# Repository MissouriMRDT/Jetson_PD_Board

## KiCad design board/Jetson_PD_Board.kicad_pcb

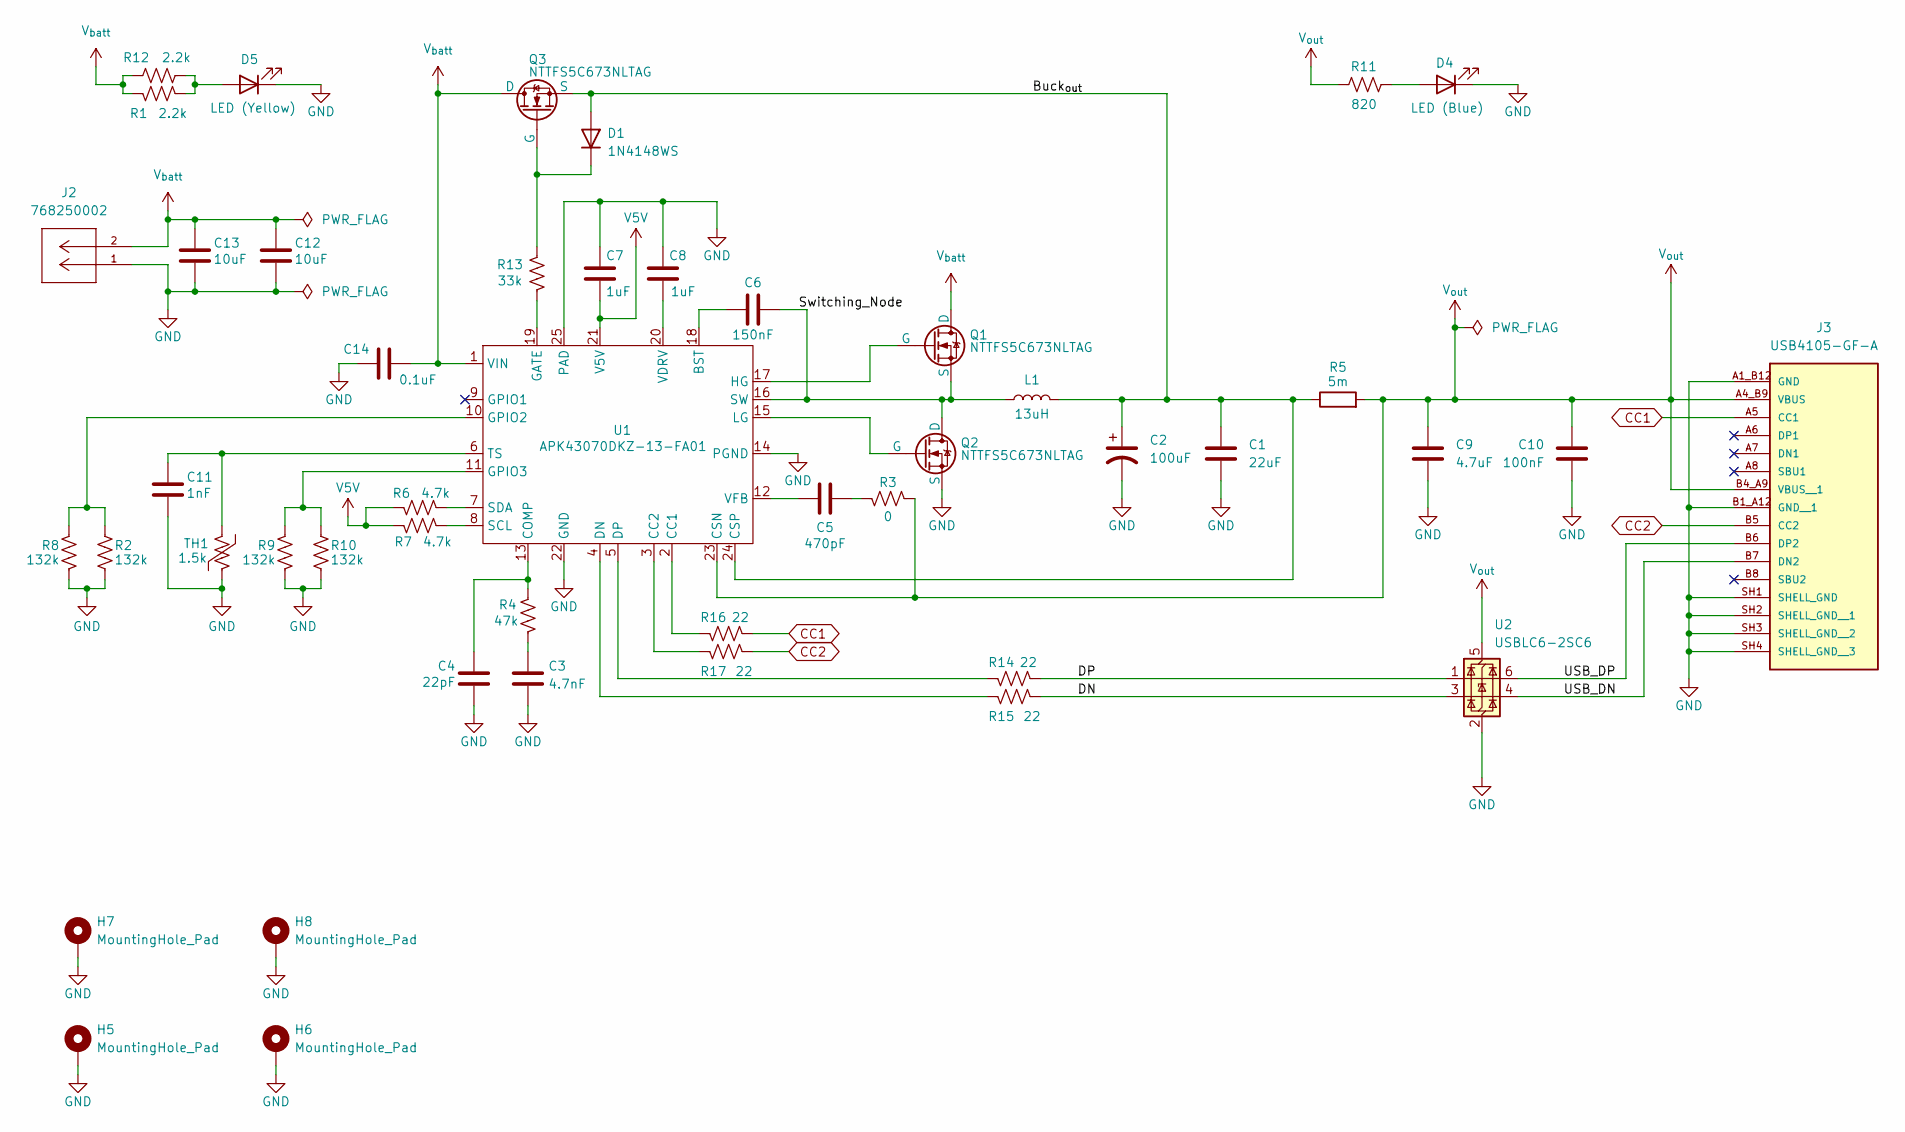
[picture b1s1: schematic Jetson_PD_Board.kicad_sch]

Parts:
C1: 22uF; C_0805_2012Metric_Pad1.18x1.45mm_HandSolder
C2: 100uF; CAP_RHA&slash_HS_8X8P7_NCH-M
C3: 4.7nF; C_0603_1608Metric_Pad1.08x0.95mm_HandSolder
C4: 22pF; C_0603_1608Metric_Pad1.08x0.95mm_HandSolder
C5: 470pF; C_0603_1608Metric_Pad1.08x0.95mm_HandSolder
C6: 150nF; C_0603_1608Metric_Pad1.08x0.95mm_HandSolder
C7, C8: 1uF; C_0603_1608Metric_Pad1.08x0.95mm_HandSolder
C9: 4.7uF; C_0603_1608Metric_Pad1.08x0.95mm_HandSolder
C10: 100nF; C_0603_1608Metric_Pad1.08x0.95mm_HandSolder
C11: 1nF; C_0603_1608Metric_Pad1.08x0.95mm_HandSolder
C12, C13: 10uF; C_1206_3216Metric_Pad1.33x1.80mm_HandSolder
C14: 0.1uF; C_0603_1608Metric_Pad1.08x0.95mm_HandSolder
D1: 1N4148WS; D_SOD-323
D4: LED (Blue); LED_0603_1608Metric
D5: LED (Yellow); LED_0603_1608Metric
H5, H6, H7, H8: MountingHole_Pad; MountingHole_3.2mm_M3_ISO14580_Pad_TopBottom
J2: 768250002; CONN_SD-76825-0100_02_MOL; MANUFACTURER_PART_NUMBER 768250002
J3: USB4105-GF-A; GCT_USB4105-GF-A; PARTREV B4
L1: 13uH; WE-PDF_1064
Q1, Q2, Q3: NTTFS5C673NLTAG; TRANS_NVTFS5116PLTAG
R1, R12: 2.2k; R_0603_1608Metric_Pad0.98x0.95mm_HandSolder
R2, R8, R9, R10: 132k; R_0603_1608Metric_Pad0.98x0.95mm_HandSolder
R3: 0; R_0603_1608Metric_Pad0.98x0.95mm_HandSolder
R4: 47k; R_0603_1608Metric_Pad0.98x0.95mm_HandSolder
R5: 5m; R_2512_6332Metric_Pad1.40x3.35mm_HandSolder
R6, R7: 4.7k; R_0603_1608Metric_Pad0.98x0.95mm_HandSolder
R11: 820; R_0603_1608Metric_Pad0.98x0.95mm_HandSolder
R13: 33k; R_0603_1608Metric_Pad0.98x0.95mm_HandSolder
R14, R15, R16, R17: 22; R_0603_1608Metric_Pad0.98x0.95mm_HandSolder
TH1: 1.5k; R_0603_1608Metric_Pad0.98x0.95mm_HandSolder
U1: APK43070DKZ-13-FA01; IC_AP33771DKZ-13
U2: USBLC6-2SC6; SOT-23-6

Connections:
/Buck_{out}: C1.1, C2.1, D1.2 (A), L1.2, Q3.3 (S), R5.1, U1.24 (CSP)
/DN: R15.2, U2.3 (I/O2)
/DP: R14.2, U2.1 (I/O1)
/Switching_Node: C6.1, L1.1, Q1.3 (S), Q2.1 (D), U1.16 (SW)
/USB_DN: J3.B7 (DN2), U2.4 (I/O2)
/USB_DP: J3.B6 (DP2), U2.6 (I/O1)
CC1: J3.A5 (CC1), R16.2
CC2: J3.B5 (CC2), R17.2
GND: C1.2, C2.2, C3.2, C4.2, C7.2, C8.2, C9.2, C10.2, C11.2, C12.2, C13.2, C14.2, D4.1 (K), D5.1 (K), H5.1, H6.1, H7.1, H8.1, J2.1, J3.A1_B12 (GND), J3.B1_A12 (GND__1), J3.SH1 (SHELL_GND), J3.SH2 (SHELL_GND__1), J3.SH3 (SHELL_GND__2), J3.SH4 (SHELL_GND__3), Q2.3 (S), R2.2, R8.2, R9.2, R10.2, TH1.2, U1.14 (PGND), U1.22 (GND), U1.25 (PAD), U2.2 (GND)
unnamed: C3.1, R4.2
unnamed: C5.1, R3.1
unnamed: D1.1 (K), Q3.2 (G), R13.2
unnamed: D4.2 (A), R11.2
unnamed: D5.2 (A), R1.2, R12.2
unnamed: Q1.2 (G), U1.17 (HG)
unnamed: Q2.2 (G), U1.15 (LG)
unnamed: C6.2, U1.18 (BST)
unnamed: R16.1, U1.2 (CC1)
unnamed: R17.1, U1.3 (CC2)
unnamed: C4.1, R4.1, U1.13 (COMP)
unnamed: R15.1, U1.4 (DN)
unnamed: R14.1, U1.5 (DP)
unnamed: R13.1, U1.19 (GATE)
unnamed: R2.1, R8.1, U1.10 (GPIO2)
unnamed: R9.1, R10.1, U1.11 (GPIO3)
unnamed: R7.2, U1.8 (SCL)
unnamed: R6.2, U1.7 (SDA)
unnamed: C11.1, TH1.1, U1.6 (TS)
unnamed: C8.1, U1.20 (VDRV)
unnamed: C5.2, U1.12 (VFB)
V5V: C7.1, R6.1, R7.1, U1.21 (V5V)
V_{batt}: C12.1, C13.1, C14.1, J2.2, Q1.1 (D), Q3.1 (D), R1.1, R12.1, U1.1 (VIN)
V_{out}: C9.1, C10.1, J3.A4_B9 (VBUS), J3.B4_A9 (VBUS__1), R3.2, R5.2, R11.1, U1.23 (CSN), U2.5 (VBUS)

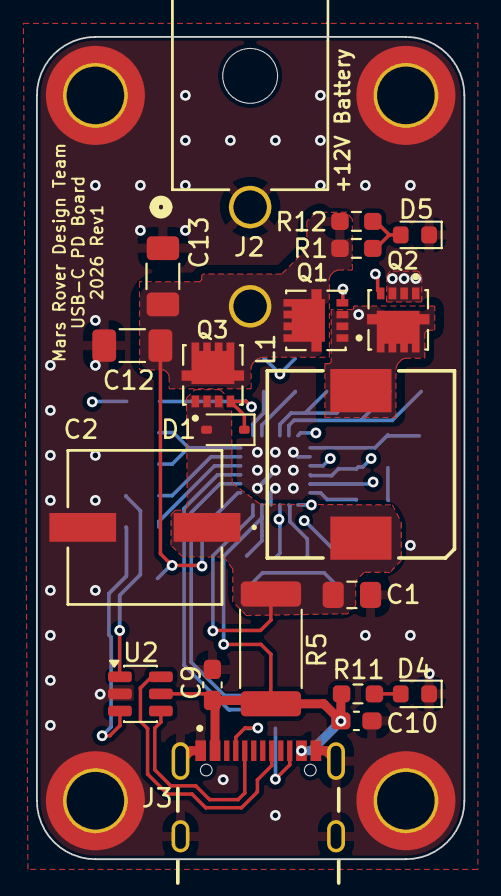
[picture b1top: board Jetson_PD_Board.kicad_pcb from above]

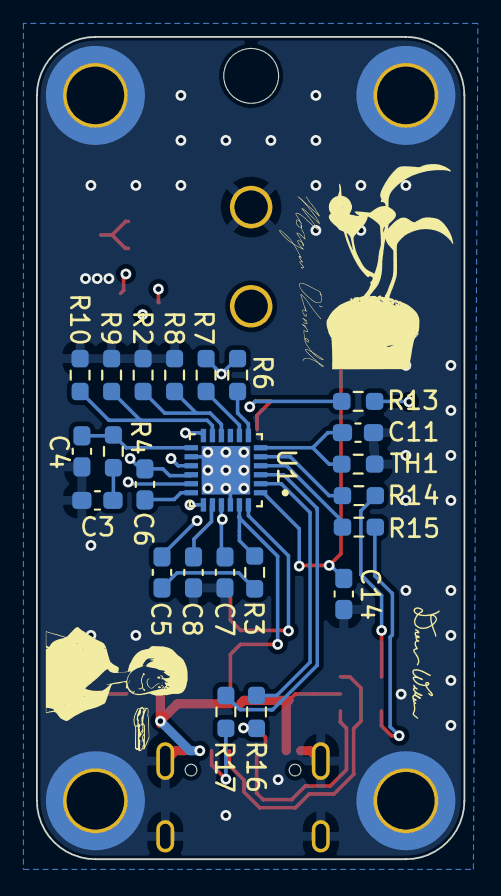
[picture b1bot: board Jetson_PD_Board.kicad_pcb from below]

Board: 4 copper layers, 23.8 x 45.7 mm, 47 parts (23 on the bottom side), 33 nets.

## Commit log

2026-02-10 Test Commit
2026-02-10 Copied Altium version into KiCAD
2026-02-10 Added GPIO 3 resistor
2026-02-11 Updated inductor value
2026-02-13 Added MOSFETs
2026-02-13 Configured GPIO pins
2026-02-13 Added thermister datasheet
2026-02-20 Added compensation network
2026-02-24 Finished connecting pins of main IC
2026-02-24 Fixed compensation loop
2026-02-26 File path adjustment attempt
2026-02-26 Changed save file name
2026-02-26 Removed duplicate file
2026-02-26 Rearranged files
2026-02-26 Fixed duplicates
2026-02-26 Removed absolute file pointer
2026-02-26 Thnx Jesse
2026-02-26 Fixed footprint library paths
2026-02-26 Double fixed footprint file paths
2026-02-26 Added Power Connector
2026-02-27 finished schematic maybe
2026-02-27 Added all footprints and 3D models
2026-02-27 Fixed ERC errors
2026-02-28 Started layout! :)
2026-02-28 Fixed 3D model file path
2026-02-28 Fixed 3d all 3D model file paths
2026-02-28 Began placing components
2026-02-28 Fixed missing pad gnd
2026-02-28 Labeled switching node
2026-02-28 Added mounting holes, indicator LED, and cleaned up shcematic
2026-02-28 Updated schematic in accordance with design guide
2026-02-28 Switch-node placement
2026-03-02 Buck component placement
2026-03-02 Worked on layout
2026-03-03 Placed most components
2026-03-03 Reviewed first placement and ordered signals on back
2026-03-03 Moved IC and passives in layout
2026-03-03 Adjusted grid
2026-03-04 Arranged power components
2026-03-05 Rearranged layout to be longer
2026-03-06 Finished new layout before routing
2026-03-06 Started routing power planes
2026-03-11 aaaaaaaaaaaaaaaaaaaaaaaaA
2026-03-12 Trace routing!
2026-03-13 Place components for a new arrangement for control IC
2026-03-13 More trace routing
2026-03-13 Connected USB-C shield to GND
2026-03-13 Finished routing before DRC
2026-03-13 Grounded mounting holes
2026-03-13 Fixed polygon discontinuity
2026-03-13 Placed silk screens and fixed minor issues
2026-03-13 Began fixing DRC errors
2026-03-16 Fixed a few DRC errors
2026-03-16 Resolved DRC violations
2026-03-16 Fixed USB-C library footprint
2026-03-16 ADDED GRETTA and signiture :)
2026-03-16 Added samnich
2026-03-16 Finished silkscreen
2026-03-17 Changes during review
2026-03-23 Updated design to ordered state.
2026-04-01 Fix Vbus shorted to GND
